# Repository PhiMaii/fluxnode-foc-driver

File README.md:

# FluxNode-FOC

FluxNode-FOC is a compact, general-purpose BLDC motor controller designed for field-oriented control in robotics, actuators, experimental drives, and motor-integrated applications.

The project combines a high-performance STM32G4 microcontroller, a three-phase MOSFET power stage, three-phase current sensing, rotor position sensing, phase-voltage measurement, CAN-FD communication, USB, temperature monitoring, and an optional brake chopper.

The design is intended to be understandable, repairable, and extensible rather than optimized only for minimum cost or minimum PCB area.

> **Project status:** Hardware and firmware architecture are still under development. Electrical values, component selections, interfaces, and PCB details may change before the first validated hardware revision.

---

## 1. Main design targets

| Parameter | Target |
|---|---:|
| Battery voltage | Up to 8S Li-ion/LiPo |
| Maximum normal battery voltage | 33.6 V |
| Design measurement range | Up to approximately 40 V |
| Nominal development voltage | 24 V |
| Continuous phase current target | Approximately 8 A RMS |
| Peak current target | Approximately 20 A |
| PWM frequency | 25 kHz |
| Control method | Field-oriented control |
| Power MOSFET voltage rating | 60 V |
| Bulk capacitor voltage rating | 50–63 V |
| Main communication interface | CAN-FD |
| MCU | STM32G474RE |
| Gate driver | DRV8323SRTAR |
| Main rotor encoder | AS5047P |
| PCB stackup | 6 layers preferred |

The controller is designed around **8S operation**, not 10S. A fully charged 8S battery reaches 33.6 V. Additional margin is required for wiring inductance, regenerative braking, switching transients, and load-disconnect events.

The system may be operated from lower voltages, including a 24 V laboratory supply, as long as the supply is compatible with regenerative energy or appropriate braking and overvoltage protection are provided.

---

## 2. Design philosophy

The main design priorities are:

1. Reliable and accurately timed current measurement for FOC.
2. Low-inductance power-stage layout.
3. Sufficient voltage margin for an 8S battery system.
4. Good observability through current, voltage, temperature, and diagnostic measurements.
5. Expandability for different motors, sensors, and actuator configurations.
6. Firmware that is understandable and not tightly coupled to a single framework.
7. Practical assembly and debugging with commonly available tools.

The design intentionally includes features that are not strictly required for basic FOC, such as phase-voltage sensing, several temperature channels, CAN-FD, an auxiliary sensor interface, and an optional brake chopper. These features make the controller more useful as a development platform and provide additional diagnostic and protection options.

---

## 3. System architecture

The controller is divided into the following main functional blocks:

- Power input and protection
- Auxiliary power supplies
- STM32G474 control section
- DRV8323 gate driver
- Three-phase MOSFET bridge
- Three-phase current measurement
- Phase-voltage and DC-bus voltage measurement
- Rotor-position sensing
- Temperature monitoring
- CAN-FD and USB communication
- Optional external sensor interfaces
- Optional brake chopper
- Fan and debug outputs

The KiCad schematic should remain split into logical hierarchical sheets rather than placing the entire design on one sheet.

Suggested schematic sheets:

```text
Power Input
Power Supplies
MCU Core
Gate Driver
Power Stage
Current Sense
Voltage Sense
Encoders and Sensors
CAN and USB
Temperature and Fan
Brake Chopper
Debug and Expansion
```

---

## 4. Microcontroller

The selected MCU is the **STM32G474RE**, based on the STM32G4 family.

Reasons for selecting this MCU include:

- High-performance Cortex-M4 core
- Floating-point unit
- Advanced motor-control timers
- Multiple fast ADCs
- Internal operational amplifiers and comparators
- CORDIC and FMAC accelerators
- Multiple SPI peripherals
- FDCAN support
- USB device support
- DAC outputs
- Good support through STM32CubeMX and STM32Cube firmware packages

The STM32G474xB/xC/xE datasheet is the reference MCU datasheet for this project.

### Motor-control timer

TIM1 is reserved for the three-phase complementary PWM outputs.

The current pin allocation uses:

- TIM1 channel 2 and channel 2N
- TIM1 channel 3 and channel 3N
- TIM1 channel 4 and channel 4N

TIM1 channel 4 on the selected STM32G474 package has a complementary output and can therefore be used as one of the three half-bridge PWM channels.

TIM1 should be configured for:

- Center-aligned PWM
- Complementary outputs
- Programmable dead time
- Break input support
- 25 kHz switching frequency
- ADC trigger generation at defined points in the PWM cycle

The exact output polarity and idle states must match the DRV8323 input configuration.

---

## 5. Gate driver

The selected gate driver is the **DRV8323SRTAR**.

It provides:

- Three half-bridge gate-drive channels
- SPI configuration and diagnostics
- Adjustable gate-drive strength
- Current-shunt amplifier support
- Fault reporting
- Undervoltage and overcurrent protection features

The gate driver is connected to the STM32 through:

- Six PWM signals
- SPI clock, COPI, CIPO, and chip select
- Enable signal
- nFAULT signal
- Optional additional diagnostic signals
- Analog VREF generated by an MCU DAC

### Gate-driver SPI

The gate driver shares SPI1 with the onboard magnetic encoder. Each device has a separate chip-select signal and is accessed sequentially.

This sharing is acceptable because neither device requires continuous full-bandwidth SPI traffic. Motor-control timing must not depend on slow or blocking SPI transactions.

The external auxiliary SPI connector uses SPI3 so that optional external hardware does not disturb the main gate-driver and encoder bus.

### nFAULT

The gate-driver fault output should be connected to an interrupt-capable GPIO input.

Software should log and decode the driver fault registers, but hardware protection must not rely only on software response time. Where practical, the timer break input should be used for immediate PWM shutdown.

### VREF

The DRV8323 current-sense amplifier reference is generated by a DAC output from the STM32 rather than being permanently tied to 3.3 V.

This allows the current-sense zero point to be adjusted in firmware. The DAC output must be properly decoupled and kept quiet because noise on VREF directly affects all current measurements.

---

## 6. Power stage

The three-phase inverter uses six external N-channel MOSFETs.

The currently selected phase MOSFET is:

- **TPW1R306PL**

The design uses 60 V MOSFETs to provide useful margin above the 33.6 V maximum battery voltage. This margin is still not sufficient by itself to tolerate uncontrolled regenerative voltage rise or poor PCB layout, so transient suppression and bus-voltage monitoring remain necessary.

### Power-stage layout priorities

The following loops must be kept as small as possible:

- High-side MOSFET, low-side MOSFET, and local ceramic/bulk capacitor commutation loop
- Gate-driver source and sink loops
- Bootstrap capacitor loops
- Current-shunt measurement loops

The gate driver and gate resistors must be placed close to the MOSFETs. Gate traces should be short, direct, and separated from high-current switching nodes.

Kelvin source connections should be used where practical for gate-drive return and current measurement.

The phase nodes are high-dV/dt switching nodes and should have limited copper area. They should not run beneath sensitive analog circuits, the encoder, the crystal, USB, or communication interfaces.

---

## 7. Power input and voltage protection

The input stage is designed for an 8S battery or a suitable DC supply.

Required or planned protection includes:

- Reverse-polarity protection where practical
- Input fuse or external fused supply
- TVS diode or equivalent transient suppression
- Local ceramic decoupling close to the bridge
- 50–63 V rated bulk capacitors
- DC-bus voltage measurement
- Firmware overvoltage and undervoltage limits
- Optional brake chopper
- Consideration of regenerative current into the source

The exact TVS voltage must be selected together with the maximum allowed bus voltage, MOSFET rating, gate-driver rating, and expected transient energy. It must not clamp during normal 8S operation but must act before the power stage is exposed to unsafe voltage.

A bench supply may not be able to absorb regenerative current. Motor deceleration can therefore raise the bus voltage even when the controller is powered from a regulated supply.

---

## 8. Current sensing

The design measures all three phase currents.

Each phase has its own shunt measurement path, allowing:

- Three-phase current reconstruction
- More flexible sampling
- Better diagnostics
- Detection of measurement inconsistencies
- Improved operation in modulation regions where two-shunt measurement becomes difficult

The phase-current channels are distributed across separate ADCs where possible so that they can be sampled simultaneously or with minimal timing skew.

The current measurements are configured as injected ADC conversions triggered by TIM1. Sampling should occur at a defined low-noise point in the PWM cycle.

Important requirements:

- Use differential/Kelvin routing from each shunt.
- Keep current-sense traces away from phase nodes and gate traces.
- Place input filtering near the receiving amplifier or ADC input as appropriate.
- Keep the three channels electrically symmetrical.
- Calibrate current offsets before enabling the power stage.
- Recheck offsets when temperature or VREF changes significantly.
- Detect ADC saturation and implausible current combinations.

Phase-current ADCs should remain the highest-priority analog measurements. Slower signals such as temperature and battery voltage should use regular conversions or lower-priority ADC resources.

---

## 9. Phase-voltage sensing

All three motor phases are measured through resistor dividers.

Phase-voltage sensing is not required for basic encoder-based FOC, but it provides several useful capabilities:

- Back-EMF observation
- Sensorless experimentation
- Motor-state diagnostics
- Phase-disconnection detection
- Verification of switching behavior
- Improved startup and fault analysis
- Potential observer development

The chosen divider concept uses two series high-side resistors and one low-side resistor to distribute voltage stress and improve routing.

The currently considered common value set is:

```text
High side: 2 × 51 kΩ
Low side: 6.8 kΩ
```

This ratio provides margin for phase and bus voltage excursions near 40 V while keeping the ADC voltage within the 3.3 V domain.

The final divider values must be verified against:

- ADC absolute maximum voltage
- Resistor tolerance
- Maximum expected transient voltage
- ADC input leakage
- Sampling-time requirements
- Desired measurement bandwidth

A small capacitor at the ADC-side divider node provides anti-aliasing and switching-noise filtering. A value around **1 nF** is currently considered for the phase-voltage channels, subject to final simulation and measurement.

The divider resistors should be placed close to the phase-sense pickup, while the final filter capacitor and any small series protection resistor should be placed close to the MCU ADC input. Routing between the divider and MCU must avoid switching nodes.

The phase voltages should be sampled from a timer-derived trigger at a repeatable point in the PWM cycle. They do not necessarily need the same timing priority as the phase currents.

---

## 10. DC-bus voltage sensing

The battery/DC-bus voltage is measured by an external resistor divider connected to an ADC channel.

The MCU VBAT pin is not used for measuring the motor supply. The external motor bus can reach approximately 40 V during transients and requires a dedicated divider.

The bus-voltage channel is used for:

- Undervoltage protection
- Overvoltage protection
- Brake-chopper control
- Regenerative-braking management
- Power and energy estimation
- Supply diagnostics

The same general divider ratio as the phase-voltage measurement may be used to simplify the bill of materials:

```text
High side: 2 × 51 kΩ
Low side: 6.8 kΩ
```

The bus voltage changes much more slowly than the phase-node voltage, so it should use stronger filtering than the phase-voltage channels. The final capacitor value should be chosen based on the desired brake-chopper response and ADC sampling rate.

The divider must be connected directly to the actual power-stage DC bus rather than to a remote or lightly loaded supply node.

---

## 11. Rotor-position sensing

The main onboard rotor encoder is the **AS5047P**.

It is connected by SPI and is intended to provide the rotor angle used by the FOC algorithm.

Reasons for choosing the AS5047P include:

- 14-bit absolute angle output
- High-speed SPI interface
- Suitability for motor-control applications
- On-chip dynamic angle error compensation
- Diagnostic information
- Common use in compact BLDC actuators

The encoder shares SPI1 with the DRV8323, using a separate chip-select signal.

Encoder transactions should be:

- Short
- Deterministic
- Checked for communication and parity errors
- Scheduled so they do not interfere with the current-control interrupt

DMA may be added later if it measurably improves timing or CPU load, but it is not required for initial firmware bring-up.

The PCB must respect the encoder manufacturer's magnet alignment, air-gap, magnetic-field, and keepout recommendations.

An additional external sensor interface is available through SPI3. This may be used for:

- A second encoder
- An off-axis sensor
- An external actuator sensor
- Experimental sensors

The external sensor is optional and not required for initial operation.

---

## 12. ADC allocation philosophy

The STM32G474 provides multiple ADCs, which are used to separate timing-critical and slow measurements.

The allocation philosophy is:

- Distribute the three phase-current measurements across ADC1, ADC2, and ADC3 where possible.
- Use injected conversions triggered by TIM1 for phase currents.
- Place phase-voltage measurements on available ADC channels, even when one ADC must contain two phase-voltage channels.
- Use regular conversions for bus voltage and temperature measurements.
- Use ADC4 and ADC5 for lower-priority auxiliary measurements where convenient.
- Avoid sacrificing correct phase-current timing merely to make the ADC channel allocation look symmetrical.

Current and phase-voltage measurements may share an ADC if the injected and regular sequences are configured carefully. The timing-critical current conversion always has priority.

---

## 13. Temperature monitoring

Planned temperature measurements include:

- Power MOSFET temperature
- Motor temperature
- Brake-chopper resistor or chopper-stage temperature
- MCU internal temperature

External temperatures are measured with NTC resistor dividers connected to ADC inputs.

Temperature monitoring is used for:

- Warning thresholds
- Current derating
- Fan control
- Controlled shutdown
- Fault logging

The MCU internal temperature sensor can be sampled in addition to the external channels. It is useful for board-level thermal monitoring but does not replace a sensor close to the MOSFETs.

NTC channels are slow signals and do not require timer-synchronous sampling.

---

## 14. Brake chopper

An optional brake chopper is included to prevent excessive DC-bus voltage during regenerative braking.

The brake chopper consists of:

- A power MOSFET
- Gate-drive circuitry
- An external or onboard braking resistor connection
- Bus-voltage feedback
- Temperature monitoring where practical
- Firmware control and fault limits

The braking resistor may be implemented as an external add-on connected through a dedicated power connector. This avoids placing a large, hot resistor on the compact controller PCB.

The chopper is controlled from a timer PWM output. It is currently assigned separately from the fan PWM so that both functions can operate independently.

The chopper is activated based on the measured DC-bus voltage. Typical firmware behavior will include:

1. Chopper remains off below the activation threshold.
2. PWM duty increases when the bus exceeds the target voltage.
3. Duty is reduced as the bus voltage falls.
4. A higher emergency threshold disables motor PWM if the chopper cannot control the bus.
5. Temperature and maximum duty limits protect the MOSFET and resistor.

The exact voltage thresholds depend on the final TVS selection, capacitor rating, MOSFET margin, and maximum permitted bus voltage.

The brake chopper must default to off during reset and startup.

---

## 15. Communication interfaces

### CAN-FD

CAN-FD is the main external real-time communication interface.

It is intended for:

- Commands and setpoints
- Telemetry
- Fault reporting
- Parameter configuration
- Multi-axis systems
- Daisy-chain-style wiring between actuator nodes

Electrical CAN wiring is a bus, not a logical point-to-point daisy chain. Connectors may provide CAN in and CAN out for convenient physical chaining, but all nodes share the same differential bus.

The controller should include:

- CAN transceiver
- CANH and CANL routing as a differential pair
- Optional switchable termination
- ESD protection near the connector
- Ground reference
- Suitable connector pinout for repeated nodes

Termination should only be enabled at the two physical ends of the CAN bus.

### USB-C

USB-C provides a local interface for:

- Firmware development
- Configuration
- Diagnostics
- Bootloader or device firmware update
- High-rate local telemetry where useful

USB is not intended to power the motor stage.

The USB section includes:

- USB 2.0 full-speed D+ and D−
- 22 Ω series resistors close to the MCU
- ESD protection close to the connector
- Correct USB-C CC resistors for a device
- VBUS sensing
- Protection against unwanted back-powering when USB and the motor battery are connected simultaneously

USB 5 V and the board's main supply must not be directly tied together without a deliberate power-path design.

---

## 16. Auxiliary interfaces

The board includes optional external interfaces for future sensors and accessories.

Planned interfaces include:

- SPI3 auxiliary sensor port
- I2C sensor port
- Fan connector
- External brake-resistor connector
- SWD debugging connector
- Debug LEDs
- Optional spare GPIO or timer signals where routing permits

The external SPI port is separate from the main SPI1 bus. This prevents an optional cable-connected device from adding excessive capacitance or noise to the gate-driver and onboard-encoder interface.

I2C is intended for relatively slow optional sensors. Pull-up resistors should be configurable or removable so that multiple boards or sensor modules do not unintentionally place too many pull-ups in parallel.

---

## 17. Fan control

An external fan can be controlled through a timer PWM output.

The fan output is independent of the brake-chopper PWM.

Firmware may control fan speed based on:

- MOSFET temperature
- Motor current
- Board temperature
- Brake-chopper activity
- User configuration

The MCU pin must not directly drive a fan motor. A suitable transistor or MOSFET stage, flyback protection where required, and connector decoupling must be provided.

---

## 18. Debugging and programming

The primary programming and debugging interface is SWD.

Required signals include:

- SWDIO
- SWCLK
- NRST
- GND
- Target reference voltage
- Optional SWO

SWO should be routed if pin availability allows it, because it can provide low-overhead debug output and timing information.

Boot configuration and reset access should remain available during bring-up.

At least two debug LEDs are planned for basic status and fault indication.

---

## 19. PCB stackup and layout

A **6-layer PCB** is preferred.

Although a 4-layer design is technically possible, the small additional fabrication cost of six layers is justified by the complexity of the mixed-signal motor-control board.

A possible six-layer stackup is:

```text
L1: Components, short signals, power-stage copper
L2: Solid ground plane
L3: Power distribution
L4: Secondary power and slower signals
L5: Solid ground plane
L6: Signals and low-current components
```

The exact stackup must be selected from the PCB manufacturer's controlled stackup options.

### Reasons for using six layers

- Better uninterrupted ground references
- Easier separation of power and sensitive analog routing
- Improved return-current paths
- More practical routing around the LQFP MCU
- Better EMI performance
- Easier CAN, USB, SPI, and ADC routing
- Reduced need to split or perforate the main ground plane

### Ground strategy

The design should use a continuous ground system rather than creating isolated analog and digital ground islands.

Sensitive analog circuits should be separated by placement and return-current control, not by cutting the ground plane.

High-current power returns must not share narrow copper paths with:

- ADC reference returns
- Current-sense returns
- Encoder ground
- USB ground
- MCU decoupling returns

Use stitching vias around noisy power areas, board edges where appropriate, and layer transitions.

### Placement order

Recommended placement order:

1. MOSFET bridge and power connectors
2. DC-link capacitors
3. Gate driver and gate components
4. Current shunts and sense paths
5. MCU and decoupling
6. Encoder
7. Power supplies
8. CAN and USB
9. Auxiliary connectors
10. Debug and low-priority circuitry

The power-stage layout should be completed before general digital routing.

---

## 20. Component sizes and assembly

The board uses a mixture of 0402 and 0603 passives.

General preference:

- Use 0402 where density or very low parasitic inductance matters.
- Use 0603 for resistor dividers, manually reworked parts, and components exposed to higher voltage.
- Use appropriately larger packages for high-power, high-voltage, or high-capacitance components.
- Do not select 0402 only to reduce board area if it makes probing and rework unnecessarily difficult.

For voltage dividers connected to the motor bus or phase nodes, 0603 resistors are preferred. Splitting the high-side resistance between two components reduces the voltage across each resistor and improves layout flexibility.

The PCB is intended to be assembled with solder paste, hot plate or reflow, hot air, flux, and hand rework where necessary. 0402 assembly is possible but requires careful paste control and inspection.

---

## 21. Firmware workflow

The firmware is generated initially with **STM32CubeMX** and developed in **Visual Studio Code**.

PlatformIO is not used for this project.

The intended workflow is:

1. Configure pins, clocks, ADCs, timers, DMA, communication peripherals, and middleware in STM32CubeMX.
2. Generate the STM32 project and initialization code.
3. Open and develop the generated project in Visual Studio Code.
4. Keep application code outside generated sections where possible.
5. Regenerate from CubeMX without overwriting project logic.
6. Build and debug using the selected ARM GCC/CMake or STM32-compatible toolchain.

The firmware will initially use STM32 HAL and LL drivers where appropriate. Time-critical motor-control code may use LL access or direct register operations after the basic system is validated.

### Firmware language

CubeMX generates C initialization code. The main firmware may remain primarily C, with carefully introduced C++ modules if they offer a clear architectural benefit.

The project should not depend on CubeMX generating native C++ code. C-generated peripheral initialization can be called from C++ through a compatible interface.

### Real-time priorities

Highest-priority operations include:

- PWM update
- Current sampling
- Current-control loop
- Hardware fault response

Lower-priority operations include:

- Encoder communication
- CAN processing
- USB communication
- Temperature conversion
- Logging
- Configuration storage
- User-interface functions

Blocking operations must not be used inside the fast control interrupt.

FreeRTOS is not required for the initial motor-control implementation. It may be evaluated later if the communication and application layers become complex enough to justify it.

---

## 22. Suggested repository structure

The project uses a single repository containing hardware, firmware, documentation, and tools.

```text
FluxNode-FOC/
├── README.md
├── LICENSE
├── .gitignore
├── docs/
│   ├── architecture/
│   ├── calculations/
│   ├── bring-up/
│   ├── measurements/
│   └── images/
├── hardware/
│   ├── kicad/
│   │   ├── FluxNode-FOC.kicad_pro
│   │   ├── FluxNode-FOC.kicad_sch
│   │   ├── FluxNode-FOC.kicad_pcb
│   │   └── sheets/
│   ├── libraries/
│   │   ├── symbols/
│   │   ├── footprints/
│   │   └── 3dmodels/
│   ├── production/
│   │   ├── gerbers/
│   │   ├── bom/
│   │   ├── pick-and-place/
│   │   └── assembly/
│   └── datasheets/
├── firmware/
│   ├── cubemx/
│   ├── Core/
│   ├── Drivers/
│   ├── App/
│   ├── MotorControl/
│   ├── Communication/
│   ├── BSP/
│   ├── Tests/
│   └── tools/
├── mechanical/
│   ├── cad/
│   ├── drawings/
│   └── exports/
└── scripts/
```

A monorepo is preferred because hardware and firmware revisions are tightly coupled. A tag or release can therefore identify the exact PCB, schematic, firmware, configuration, and documentation that belong together.

Generated production files should be placed in clearly versioned release folders or attached to Git releases rather than continuously overwriting unversioned files.

Large vendor libraries should not be copied into the repository unless their license permits it and they are required for reproducible builds.

---

## 23. Naming and revision conventions

Suggested conventions:

- Repository: `FluxNode-FOC`
- Firmware modules: lowercase or project-standard snake_case
- PCB revision: `REV_A`, `REV_B`, and so on
- Firmware semantic version: `v0.1.0`, `v0.2.0`, and so on
- Hardware-specific firmware configuration: explicitly tied to a PCB revision
- Nets: descriptive uppercase names such as `VBUS`, `PHASE_A`, `ISENSE_A`, and `DRV_NFAULT`

Each manufactured PCB revision should have a visible revision marking on the silkscreen.

Firmware should check or store the expected hardware revision where practical.

---

## 24. Bring-up strategy

Initial bring-up should be performed in controlled stages.

### Stage 1: Unpowered checks

- Visual inspection
- Resistance checks between all power rails and ground
- Verify MOSFET orientation
- Verify gate-driver and MCU pin orientation
- Check for solder bridges
- Check shunt and divider values
- Confirm connector polarity

### Stage 2: Low-voltage control power

- Use a current-limited supply
- Verify all regulated rails
- Confirm MCU programming and SWD
- Check reset and clock operation
- Test debug LEDs
- Verify USB without motor power

### Stage 3: Gate driver without motor operation

- Read and write SPI registers
- Confirm nFAULT behavior
- Verify DAC-generated VREF
- Observe PWM outputs with the bridge disabled
- Verify dead time and complementary polarity

### Stage 4: Power-stage switching

- Use a low DC-bus voltage
- Use strict current limiting
- Test one half bridge at a time where practical
- Observe gate voltage, switch node, and ringing
- Verify bootstrap operation
- Tune gate resistors only after measurements

### Stage 5: Sensor validation

- Calibrate current offsets
- Inject known current where possible
- Verify bus and phase-voltage scaling
- Check all NTC channels
- Verify encoder direction, zero, and diagnostics

### Stage 6: First motor operation

- Use a small motor and low bus voltage
- Start with limited voltage and current commands
- Validate phase order
- Validate encoder direction and electrical offset
- Test open-loop rotation before closed-loop current control
- Keep overcurrent and overvoltage limits conservative

### Stage 7: Full-power validation

- Increase voltage and current gradually
- Measure MOSFET and gate-driver temperature
- Validate bus transients
- Test regenerative braking
- Validate brake-chopper behavior
- Perform sustained thermal tests

---

## 25. Safety

This project controls motors from battery voltages and currents capable of causing burns, fire, component explosion, mechanical injury, and battery damage.

Development precautions include:

- Use a current-limited power source during bring-up.
- Add an appropriate fuse.
- Keep a physical emergency disconnect accessible.
- Secure the motor mechanically.
- Do not touch the board while powered.
- Use differential or isolated probing techniques for switching-node measurements.
- Do not connect an oscilloscope ground clip to a non-ground switching node.
- Treat lithium batteries as high-energy sources.
- Verify braking behavior before high-speed operation.
- Test overvoltage protection before relying on regenerative braking.

The controller is an experimental design and is not certified for safety-critical use.

---

## 26. Open design decisions

The following items are not yet final and must be confirmed before release:

- Final CAN transceiver and connector pinout
- Final auxiliary power-supply topology
- Final TVS diode and overvoltage thresholds
- Exact current-shunt resistance and power rating
- Current-sense amplifier gain and filtering
- Final voltage-divider capacitor values
- Brake-chopper MOSFET, gate driver, resistor rating, and connector
- Final fan voltage and output stage
- Exact ADC channel allocation
- Final SPI clock rates
- DMA usage for encoder and communication peripherals
- USB device class
- Final board dimensions and mounting pattern
- Final six-layer manufacturer stackup
- Exact thermal limits and current-derating curve
- Production test-point set
- Bootloader and firmware-update strategy

These items should be moved out of this section once they are validated and formally adopted.

---

## 27. Documentation policy

Important design decisions should be documented in the repository rather than existing only in chat logs or schematic comments.

For every major decision, record:

- What was selected
- Why it was selected
- Alternatives considered
- Important calculations
- Validation measurements
- Any revision-specific limitations

Hardware calculations, oscilloscope captures, thermal tests, and bring-up notes should be stored under `docs/`.

Datasheets should either be linked from documentation or stored under `hardware/datasheets/` when redistribution is permitted.

---

## 28. License

A license has not yet been finalized.

Before publishing the repository, choose separate or compatible licenses for:

- Hardware design files
- Firmware
- Documentation

Common choices include CERN-OHL for hardware and MIT, BSD, GPL, or Apache-2.0 for firmware. The final choice should reflect whether commercial reuse and closed-source derivatives are intended to be allowed.

---

## 29. Current project summary

The current FluxNode-FOC concept is a 6-layer, STM32G474-based FOC motor controller for up to 8S operation. It uses a DRV8323 SPI gate driver, external 60 V MOSFETs, three phase-current measurements, three phase-voltage measurements, DC-bus sensing, an AS5047P rotor encoder, CAN-FD, USB-C, temperature monitoring, fan control, and an optional external-resistor brake chopper.

The firmware is generated with STM32CubeMX and developed in Visual Studio Code without PlatformIO.

The project remains under active development, and all high-power functionality must be validated experimentally before the design is considered complete.

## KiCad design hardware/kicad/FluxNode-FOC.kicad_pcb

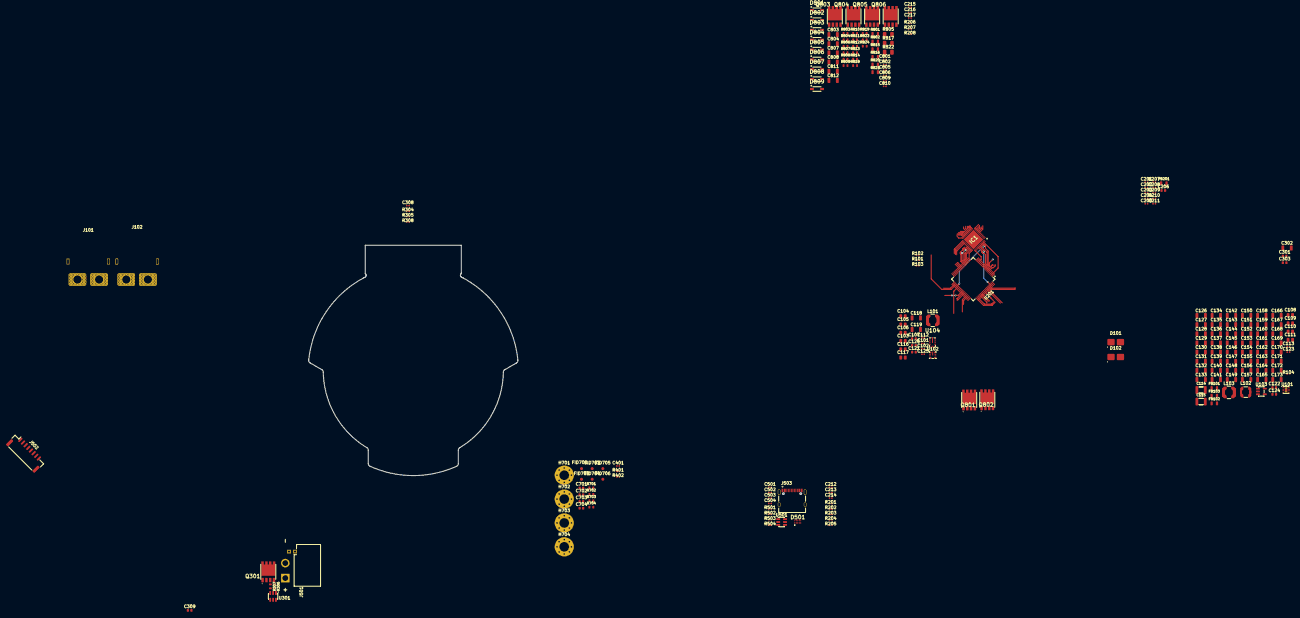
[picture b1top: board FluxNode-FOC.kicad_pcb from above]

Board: 6 copper layers, 216 parts (0 on the bottom side), 93 nets.

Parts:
C101, C102, C113: 100nF X7R 50V; C_0402_1005_DensityHigh
C103, C111: 22uF X7R 10V; C_0805_2012_DensityHigh
C104, C116: 2u2 X7R 100V; C_0805_2012_DensityHigh
C105, C106, C108, C109, C117: 2u2 100V; C_0805_2012_DensityHigh
C107, C303: 100nF 100V; C_0603_1608_DensityHigh
C110: 10u 25V; C_0805_2012_DensityHigh
C112, C201, C209: 1uF X7R 10V; C_0402_1005_DensityHigh
C114, C115: 15uF 25V; C_1210_3225_DensityHigh
C118, C119, C302: 4u7 100V; C_1206_3216_DensityHigh
C120, C121: 220n 100V; C_0603_1608_DensityHigh
C122, C301: 1u 25V; C_0603_1608_DensityHigh
C123: 10n 100V; C_0402_1005_DensityHigh
C124, C206: 4.7u 16V; C_0603_1608_DensityHigh
C125: 1u X7R 10V; C_0402_1005_DensityHigh
C126, C127, C128, C129, C130, C131, C132, C133, C134, C135, C136, C137, C138, C139, C140, C141, C142, C143, C144, C145, C146, C147, C148, C149, C150, C151, C152, C153, C154, C155, C156, C157, C158, C159, C160, C161, C162, C163, C164, C165, C166, C167, C168, C169, C170, C171, C172, C173, C803, C808, C812: 4.7u 100V; C_1206_3216_DensityHigh
C202, C203, C204, C205, C208, C210, C401: 100n 50V; C_0402_1005_DensityHigh
C207: 1uF 10V; C_0402_1005_DensityHigh
C211: 4.7u X5R 25V; C_0402_1005_DensityHigh
C212, C213, C214: 1nF 25V; C_0402_1005_DensityHigh
C215, C216, C217: 470pF 50V; C_0402_1005_DensityHigh
C308, C503, C504: 100nF 50V; C_0402_1005_DensityHigh
C309: 1uF 50V; C_0603_1608_DensityHigh
C501, C502: 100nF; C_0402_1005_DensityHigh
C701, C702, C703, C704: 1nF 1kV; C_0603_1608_DensityHigh
C801, C802, C805, C806, C809, C810: 3n3 10% 100V; C_0402_1005_DensityHigh
C804, C807, C811: 100nF 100V; C_1206_3216_DensityHigh
D101, D102: SMBJ51CD-M3_H; DIOM4336X24N
D501: PESD4USB3U-TBSX; PESD4USB3UTBSX
D801, D802, D803, D804, D805, D806, D807, D808, D809: BAT41ZFILM; SOD3816X145N
FB101, FB102, FB103, FB201: 1k @ 100MHz; R_0805_2012_DensityHigh
FID701, FID702, FID703, FID704, FID705, FID706: Fiducial; Fiducial_1mm_Mask2mm
H701, H702, H703, H704: MountingHole_Pad; MountingHole_3.2mm_M3_Pad_Via
IC1: DRV8323SRTAR; QFN50P600X600X80-41N-D
J101: XT60PW-F; AMASS_XT60PW-F_1x02_P7.20mm_Horizontal
J102: XT60PW-M; AMASS_XT60PW-M_1x02_P7.20mm_Horizontal
J501: XT30PW_2_2_-M.G.B; AMASS_XT30PW_2_2_-M.G.B
J502: Conn_01x08_Pin; JST_GH_SM08B-GHS-TB_1x08-1MP_P1.25mm_Horizontal
J503: TYPE-C-31-M-12; HRO_TYPE-C-31-M-12
L101, L103: 22uH 830mA 360mOhms; L_Coilcraft_LPS4018
L102: 2.2uH 1,2A 100mOhms; L_Coilcraft_LPS3314
Q301, Q801, Q802, Q803, Q804, Q805, Q806: TPW1R306PL; SOP_ADVANCE
R101: 10k 1% 50V; R_0402_1005_DensityHigh
R102: 0R; R_0402_1005_DensityHigh
R103: 100k 1% 50V; R_0402_1005_DensityHigh
R104: 9.09k 1% 50V; R_0402_1005_DensityHigh
R201, R202, R203, R204, R205: 22R 1%; R_0402_1005_DensityHigh
R206, R207, R208: 1K 1%; R_0402_1005_DensityHigh
R304: 100; R_0402_1005_DensityHigh
R305: 10k; R_0402_1005_DensityHigh
R306: 4.7; R_0603_1608_DensityHigh
R307: 1.5; R_0603_1608_DensityHigh
R308: 47k; R_0402_1005_DensityHigh
R401: 100k 1%; R_0402_1005_DensityHigh
R402: 8k2 1%; R_0402_1005_DensityHigh
R501, R502: 5k1 1%; R_0402_1005_DensityHigh
R503, R504: 100k; R_0402_1005_DensityHigh
R701, R702, R703, R704: 0R; R_0603_1608_DensityHigh
R801, R802, R815, R816, R820, R821: 7.5 1% 0.5W; R_0805_2012_DensityHigh
R803, R804, R818, R819, R823, R824: 5R 1% 0.4W; R_0603_1608_DensityHigh
R805, R817, R822: 0.5m 1% 2W; R_1206_3216_DensityHigh
R806, R807, R809, R810, R812, R813: 43k 1% 75V; R_0603_1608_DensityHigh
R808, R811, R814: 6k8 1% 75V; R_0603_1608_DensityHigh
U101: TPS62172DSG; WSON-8-1EP_2x2mm_P0.5mm_EP0.9x1.6mm_ThermalVias
U102: LMR36506MSC5RPERQ1; LMR36503
U103: LP2992IM5-3.3/NOPB; SOT-23-5
U104: LMR36006FSCQ; LMR36006
U201: STM32G474RET6; LQFP-64_10x10mm_P0.5mm
U301: UCC27511ADBV; SOT-23-6
U501: USBLC6-2SC6; SOT-23-6

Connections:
+3V3: C111.1, C201.1, C202.1, C203.1, C204.1, C205.1, C206.1, C503.1, L102.2, U201.1 (VBAT), U201.16 (VDD), U201.32 (VDD), U201.48 (VDD), U201.64 (VDD)
+5V: C102.1, C103.1, C108.1, C122.1, FB102.1, L101.2, R101.1, U103.1 (VIN)
+12V: C114.1, C115.1, C308.1, C309.1, L103.2, U301.1 (V_{DD})
+A3V3: C124.1, C209.1, FB201.2, IC1.24 (VREF), U103.5 (VOUT)
+VBAT: C104.1, C116.1, C126.1, C127.1, C128.1, C129.1, C130.1, C131.1, C132.1, C133.1, C134.1, C135.1, C136.1, C137.1, C138.1, C139.1, C140.1, C141.1, C142.1, C143.1, C144.1, C145.1, C146.1, C147.1, C148.1, C149.1, C150.1, C151.1, C152.1, C153.1, C154.1, C155.1, C156.1, C157.1, C158.1, C159.1, C160.1, C161.1, C162.1, C163.1, C164.1, C165.1, C166.1, C167.1, C168.1, C169.1, C170.1, C171.1, C172.1, C173.1, C301.1, C302.1, C303.1, C803.1, C804.1, C807.1, C808.1, C811.1, C812.1, D101.2, D102.2, FB101.1, FB103.1, IC1.4 (VM), IC1.5 (VDRAIN), J101.2, J102.2, J501.P, Q801.5 (D), Q801.6 (D), Q801.7 (D), Q801.8 (D), Q803.5 (D), Q803.6 (D), Q803.7 (D), Q803.8 (D), Q805.5 (D), Q805.6 (D), Q805.7 (D), Q805.8 (D), R401.1, R803.2, R818.2, R823.2
/01 Power Generation/5V_VIN_3V3: C109.1, C110.1, FB102.2, U101.2 (VIN)
/01 Power Generation/ADJ_A3V3: C123.1, U103.4 (ADJ)
/01 Power Generation/BOOT_5V: C101.2, U102.6 (BOOT)
/01 Power Generation/BOOT_12V: C113.2, U104.4 (BOOT)
/01 Power Generation/FB_DIV_12V: R103.2, R104.1, U104.7 (FB)
/01 Power Generation/F_VIN_5V: C105.1, C106.1, C107.1, FB101.2, U102.3 (EN/UVLO), U102.4 (VIN)
/01 Power Generation/F_VIN_12V: C117.1, C118.1, C119.1, C120.1, C121.1, FB103.2, U104.2 (VIN), U104.9 (EN), U104.10 (VIN)
/01 Power Generation/PG_5V: R101.2, U101.3 (EN), U102.2 (PGOOD), U103.3 (ON/~OFF)
/01 Power Generation/SW_3V3: L102.1, U101.7 (SW)
/01 Power Generation/SW_5V: C101.1, L101.1, U102.5 (SW)
/01 Power Generation/SW_12V: C113.1, L103.1, U104.3 (NC), U104.12 (SW)
/02 MCU/BRAKE_CTRL: R304.2, U201.41 (PC9)
/02 MCU/DRV_CAL: IC1.31 (CAL), U201.14 (PA2)
/02 MCU/DRV_EN: IC1.30 (ENABLE), U201.17 (PA3)
/02 MCU/DRV_PWM_HA: IC1.34 (INHA), U201.10 (PC2)
/02 MCU/DRV_PWM_HB: IC1.36 (INHB), U201.9 (PC1)
/02 MCU/DRV_PWM_HC: IC1.38 (INHC), U201.8 (PC0)
/02 MCU/DRV_PWM_LA: IC1.35 (INLA), U201.62 (PB9)
/02 MCU/DRV_PWM_LB: IC1.37 (INLB), U201.36 (PB14)
/02 MCU/DRV_PWM_LC: IC1.39 (INLC), U201.2 (PC13)
/02 MCU/DRV_SOA_FILT: C212.1, R201.1, U201.24 (PB0)
/02 MCU/DRV_SOB_FILT: C213.1, R202.1, U201.25 (PB1)
/02 MCU/DRV_SOC_FILT: C214.1, R203.1, U201.26 (PB2)
/02 MCU/DRV_nFAULT: IC1.25 (NFAULT), U201.22 (PC4)
/02 MCU/F_A3V3: C207.1, C208.1, C210.1, C211.1, FB201.1, U201.28 (VREF+), U201.29 (VDDA)
/02 MCU/NRST: C504.1, D501.1 (K), D501.10 (K), U201.7 (PG10)
/02 MCU/SENSE_UA: C215.1, R206.1, U201.11 (PC3)
/02 MCU/SENSE_UB: C216.1, R207.1, U201.13 (PA1)
/02 MCU/SENSE_UC: C217.1, R208.1, U201.12 (PA0)
/02 MCU/SENSE_VBAT: C401.1, R401.2, R402.1, U201.35 (PB13)
/02 MCU/SOA: IC1.23 (SOA), R201.2
/02 MCU/SOB: IC1.22 (SOB), R202.2
/02 MCU/SOC: IC1.21 (SOC), R203.2
/02 MCU/SPI1_DRV_CS: IC1.29 (NSCS), U201.18 (PA4)
/02 MCU/SPI1_MISO: IC1.26 (SDO), U201.20 (PA6)
/02 MCU/SPI1_MOSI: IC1.27 (SDI), U201.21 (PA7)
/02 MCU/SPI1_SCK: IC1.28 (SCLK), U201.19 (PA5)
/02 MCU/SWCLK: D501.4 (K), D501.7 (K), U201.50 (PA14)
/02 MCU/SWDIO: D501.5 (K), D501.6 (K), U201.49 (PA13)
/02 MCU/SWO: D501.2 (K), D501.9 (K), U201.56 (PB3)
/02 MCU/USB_D+: R204.1, U201.46 (PA12), U501.6 (I/O1)
/02 MCU/USB_D-: R205.1, U201.45 (PA11), U501.4 (I/O2)
/02 MCU/USB_VBUS_SENSE: C501.1, R503.1, R504.2, U201.37 (PB15)
/03 Motor Control - Brake Chopper/BRAKE_GATE: Q301.4 (G), R306.1, R307.1, R308.2
/03 Motor Control - Brake Chopper/OUTH: R306.2, U301.2 (OUTH)
/03 Motor Control - Brake Chopper/OUTL: R307.2, U301.3 (OUTL)
/03 Motor Control - Gate Driver/03 Motor Control - Inverter/FET_GH_A: D803.2 (A), Q801.4 (G), R801.2
/03 Motor Control - Gate Driver/03 Motor Control - Inverter/FET_GH_B: D805.2 (A), Q803.4 (G), R815.2
/03 Motor Control - Gate Driver/03 Motor Control - Inverter/FET_GH_C: D808.2 (A), Q805.4 (G), R820.2
/03 Motor Control - Gate Driver/03 Motor Control - Inverter/FET_GL_A: D801.1 (K), D802.2 (A), Q802.4 (G), R802.2
/03 Motor Control - Gate Driver/03 Motor Control - Inverter/FET_GL_B: D804.1 (K), D806.2 (A), Q804.4 (G), R816.2
/03 Motor Control - Gate Driver/03 Motor Control - Inverter/FET_GL_C: D807.1 (K), D809.2 (A), Q806.4 (G), R821.2
/03 Motor Control - Gate Driver/03 Motor Control - Inverter/PHA: C801.2, C802.2, Q801.1 (S), Q801.2 (S), Q801.3 (S), Q802.5 (D), Q802.6 (D), Q802.7 (D), Q802.8 (D), R806.2
/03 Motor Control - Gate Driver/03 Motor Control - Inverter/PHB: C805.2, C806.2, Q803.1 (S), Q803.2 (S), Q803.3 (S), Q804.5 (D), Q804.6 (D), Q804.7 (D), Q804.8 (D), R809.2
/03 Motor Control - Gate Driver/03 Motor Control - Inverter/PHC: C809.2, C810.2, Q805.1 (S), Q805.2 (S), Q805.3 (S), Q806.5 (D), Q806.6 (D), Q806.7 (D), Q806.8 (D), R812.2
/03 Motor Control - Gate Driver/03 Motor Control - Inverter/SNUB_HA: C801.1, R803.1
/03 Motor Control - Gate Driver/03 Motor Control - Inverter/SNUB_HB: C805.1, R818.1
/03 Motor Control - Gate Driver/03 Motor Control - Inverter/SNUB_HC: C809.1, R823.1
/03 Motor Control - Gate Driver/03 Motor Control - Inverter/SNUB_LA: C802.1, R804.1
/03 Motor Control - Gate Driver/03 Motor Control - Inverter/SNUB_LB: C806.1, R819.1
/03 Motor Control - Gate Driver/03 Motor Control - Inverter/SNUB_LC: C810.1, R824.1
/03 Motor Control - Gate Driver/03 Motor Control - Inverter/SRC_LS_A: C804.2, Q802.1 (S), Q802.2 (S), Q802.3 (S), R804.2, R805.2
/03 Motor Control - Gate Driver/03 Motor Control - Inverter/SRC_LS_B: C807.2, Q804.1 (S), Q804.2 (S), Q804.3 (S), R817.2, R819.2
/03 Motor Control - Gate Driver/03 Motor Control - Inverter/SRC_LS_C: C811.2, Q806.1 (S), Q806.2 (S), Q806.3 (S), R822.2, R824.2
/03 Motor Control - Gate Driver/GHA: D803.1 (K), IC1.6 (GHA), R801.1
/03 Motor Control - Gate Driver/GHB: D805.1 (K), IC1.15 (GHB), R815.1
/03 Motor Control - Gate Driver/GHC: D808.1 (K), IC1.16 (GHC), R820.1
/03 Motor Control - Gate Driver/GLA: D802.1 (K), IC1.8 (GLA), R802.1
/03 Motor Control - Gate Driver/GLB: D806.1 (K), IC1.13 (GLB), R816.1
/03 Motor Control - Gate Driver/GLC: D809.1 (K), IC1.18 (GLC), R821.1
/03 Motor Control - Gate Driver/SENSE_UA: R807.1, R808.2
/03 Motor Control - Gate Driver/SENSE_UB: R810.1, R811.2
/03 Motor Control - Gate Driver/SENSE_UC: R813.1, R814.2
/05 Interface - Interconnects/D+: J503.A6 (DP1), J503.B6 (DP2), U501.1 (I/O1)
/05 Interface - Interconnects/D-: J503.A7 (DN1), J503.B7 (DN2), U501.3 (I/O2)
/05 Interface - Interconnects/USB_CC1: J503.A5 (CC1), R502.1
/05 Interface - Interconnects/USB_CC2: J503.B5 (CC2), R501.1
/BRAKE_SW: J501.N, Q301.5 (D), Q301.6 (D), Q301.7 (D), Q301.8 (D)
CHASSIS: C701.1, C702.1, C703.1, C704.1, D101.1, D102.1, H701.1 (1_1), H702.1 (1_1), H703.1 (1_1), H704.1 (1_1), J101.MP2, J102.MP2, J503.S1 (SHIELD), J503.S2 (SHIELD), J503.S3 (SHIELD), J503.S4 (SHIELD), R701.1, R702.1, R703.1, R704.1
GND: C102.2, C103.2, C104.2, C105.2, C106.2, C107.2, C108.2, C109.2, C110.2, C111.2, C112.2, C114.2, C115.2, C116.2, C117.2, C118.2, C119.2, C120.2, C121.2, C122.2, C123.2, C124.2, C125.2, C126.2, C127.2, C128.2, C129.2, C130.2, C131.2, C132.2, C133.2, C134.2, C135.2, C136.2, C137.2, C138.2, C139.2, C140.2, C141.2, C142.2, C143.2, C144.2, C145.2, C146.2, C147.2, C148.2, C149.2, C150.2, C151.2, C152.2, C153.2, C154.2, C155.2, C156.2, C157.2, C158.2, C159.2, C160.2, C161.2, C162.2, C163.2, C164.2, C165.2, C166.2, C167.2, C168.2, C169.2, C170.2, C171.2, C172.2, C173.2, C201.2, C202.2, C203.2, C204.2, C205.2, C206.2, C207.2, C208.2, C209.2, C210.2, C211.2, C212.2, C213.2, C214.2, C215.2, C216.2, C217.2, C302.2, C303.2, C308.2, C309.2, C401.2, C501.2, C503.2, C504.2, C701.2, C702.2, C703.2, C704.2, C803.2, C808.2, C812.2, D501.3 (A), D501.8 (A), D801.2 (A), D804.2 (A), D807.2 (A), IC1.32 (AGND), IC1.40 (PGND), IC1.41 (EP), J101.1, J102.1, J503.A1_B12 (GND), J503.B1_A12 (GND), Q301.1 (S), Q301.2 (S), Q301.3 (S), R102.2, R104.2, R305.1, R308.1, R402.2, R501.2, R502.2, R504.1, R701.2, R702.2, R703.2, R704.2, R805.1, R808.1, R811.1, R814.1, R817.1, R822.1, U101.1 (PGND), U101.4 (AGND), U101.5 (FB), U101.9 (PAD), U102.9 (GND), U103.2 (GND), U104.1 (PGND), U104.6 (AGND), U104.11 (PGND), U201.15 (VSS), U201.27 (VSSA), U201.31 (VSS), U201.47 (VSS), U201.63 (VSS), U301.4 (GND), U301.5 (IN-), U501.2 (GND)
unnamed: C301.2, IC1.3 (VCP)
unnamed: R806.1, R807.2
unnamed: R809.1, R810.2
unnamed: R812.1, R813.2
unnamed: C112.1, R102.1, U102.1 (MODE/SYNC)
unnamed: C125.1, U104.5 (VCC)
unnamed: R304.1, R305.2, U301.6 (IN+)
VBUS: C502.1, J503.A4_B9 (VBUS), J503.B4_A9 (VBUS), R503.2, U501.5 (VBUS)

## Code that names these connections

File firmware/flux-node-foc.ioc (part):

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Mcu.Name=STM32G474R(B-C-E)Tx
Mcu.Package=LQFP64
Mcu.UserName=STM32G474RETx
PA0.GPIOParameters=GPIO_Label
PA0.GPIO_Label=SENSE_U_C
PA0.Mode=IN1-Single-Ended
PA0.Signal=ADC2_IN1
PA1.GPIOParameters=GPIO_Label
PA1.GPIO_Label=SENSE_U_B
PA1.Mode=IN2-Single-Ended
PA1.Signal=ADC1_IN2
PA11.Mode=Device
PA11.Signal=USB_DM
PA12.Mode=Device
PA12.Signal=USB_DP
PA13.Mode=Trace_Asynchronous_SW
PA13.Signal=SYS_JTMS-SWDIO
PA14.Mode=Trace_Asynchronous_SW
PA14.Signal=SYS_JTCK-SWCLK
PA2.GPIOParameters=GPIO_Label
PA2.GPIO_Label=DRV_CAL
PA2.Signal=GPIO_Output
PA3.GPIOParameters=GPIO_Label
PA3.GPIO_Label=DRV_EN
PA3.Signal=GPIO_Output
PA4.GPIOParameters=GPIO_Speed,GPIO_Label
PA4.GPIO_Label=SPI1_DRV_CS
PA4.GPIO_Speed=GPIO_SPEED_FREQ_MEDIUM
PA4.Signal=GPIO_Output
PA5.Mode=Full_Duplex_Master
PA5.Signal=SPI1_SCK
PA6.Mode=Full_Duplex_Master
PA6.Signal=SPI1_MISO
PA7.Mode=Full_Duplex_Master
PA7.Signal=SPI1_MOSI
PA8.GPIOParameters=GPIO_Label
PA8.GPIO_Label=SENSE_TEMP_FET
PA8.Mode=IN1-Single-Ended
PA8.Signal=ADC5_IN1
PA9.GPIOParameters=GPIO_Label
PA9.GPIO_Label=SENSE_TEMP_MOT
PA9.Mode=IN2-Single-Ended
PA9.Signal=ADC5_IN2
PB0.GPIOParameters=GPIO_Label
PB0.GPIO_Label=DRV_SOA
PB0.Mode=IN12-Single-Ended
PB0.Signal=ADC3_IN12
PB1.GPIOParameters=GPIO_Label
PB1.GPIO_Label=DRV_SOB
PB1.Mode=IN12-Single-Ended
PB1.Signal=ADC1_IN12
PB11.GPIOParameters=GPIO_Label
PB11.GPIO_Label=EXT_FAN
PB11.Signal=S_TIM2_CH4
PB12.GPIOParameters=GPIO_Label
PB12.GPIO_Label=SENSE_TEMP_BRAKE
PB12.Mode=IN3-Single-Ended
PB12.Signal=ADC4_IN3
PB13.GPIOParameters=GPIO_Label
PB13.GPIO_Label=SENSE_VBAT
PB13.Mode=IN5-Single-Ended
PB13.Signal=ADC3_IN5
PB14.GPIOParameters=GPIO_Label
PB14.GPIO_Label=DRV_PWM_LB
PB14.Mode=PWM Generation2 CH2 CH2N
PB14.Signal=TIM1_CH2N
PB15.GPIOParameters=GPIO_Label
PB15.GPIO_Label=SENSE_USB_VBUS
PB15.Mode=IN5-Single-Ended
PB15.Signal=ADC4_IN5
PB2.GPIOParameters=GPIO_Label
PB2.GPIO_Label=DRV_SOC
PB2.Mode=IN12-Single-Ended
PB2.Signal=ADC2_IN12
PB3.Mode=Trace_Asynchronous_SW
PB3.Signal=SYS_JTDO-SWO
PB4.GPIOParameters=GPIO_Label
PB4.GPIO_Label=LED_PWR
PB4.Signal=GPIO_Output
PB5.Mode=FDCAN_Activate
PB5.Signal=FDCAN2_RX
PB6.Mode=FDCAN_Activate
PB6.Signal=FDCAN2_TX
PB7.Mode=I2C
PB7.Signal=I2C1_SDA
PB8-BOOT0.Mode=I2C
PB8-BOOT0.Signal=I2C1_SCL
PB9.GPIOParameters=GPIO_Label,GPIO_FM9
PB9.GPIO_FM9=__NULL
PB9.GPIO_Label=DRV_PWM_LA
PB9.Mode=PWM Generation3 CH3 CH3N
PB9.Signal=TIM1_CH3N
PC0.GPIOParameters=GPIO_Label
PC0.GPIO_Label=DRV_PWM_HC
PC0.Signal=S_TIM1_CH1
PC1.GPIOParameters=GPIO_Label
PC1.GPIO_Label=DRV_PWM_HB
PC1.Signal=S_TIM1_CH2
PC10.Mode=Full_Duplex_Master
PC10.Signal=SPI3_SCK
PC11.Mode=Full_Duplex_Master
PC11.Signal=SPI3_MISO
PC12.Mode=Full_Duplex_Master
PC12.Signal=SPI3_MOSI
PC13.GPIOParameters=GPIO_Label
PC13.GPIO_Label=DRV_PWM_LC
PC13.Mode=PWM Generation1 CH1 CH1N
PC13.Signal=TIM1_CH1N
PC14-OSC32_IN.GPIOParameters=GPIO_Label
PC14-OSC32_IN.GPIO_Label=SPI1_AUX1_CS
PC14-OSC32_IN.Signal=GPIO_Output
PC2.GPIOParameters=GPIO_Label
PC2.GPIO_Label=PWM_DRV_HA
PC2.Signal=S_TIM1_CH3
PC3.GPIOParameters=GPIO_Label
PC3.GPIO_Label=SENSE_U_A
PC3.Mode=IN9-Single-Ended
PC3.Signal=ADC2_IN9
PC4.GPIOParameters=GPIO_Label
PC4.GPIO_Label=DRV_nFAULT
PC4.Signal=GPXTI4
PC5.GPIOParameters=GPIO_Speed,GPIO_Label
PC5.GPIO_Label=SPI1_MAG_CS
PC5.GPIO_Speed=GPIO_SPEED_FREQ_MEDIUM
PC5.Signal=GPIO_Output
PC9.GPIOParameters=GPIO_Label
PC9.GPIO_Label=BRAKE_PWM
PC9.Signal=S_TIM3_CH4
PD2.GPIOParameters=GPIO_Label
PD2.GPIO_Label=LED_DBG
PD2.Signal=GPIO_Output
PF0-OSC_IN.Mode=HSE-External-Oscillator
PF0-OSC_IN.Signal=RCC_OSC_IN
PF1-OSC_OUT.Mode=HSE-External-Oscillator
PF1-OSC_OUT.Signal=RCC_OSC_OUT
RCC.HSE_VALUE=8000000
RCC.SYSCLKFreq_VALUE=170000000
RCC.SYSCLKSource=RCC_SYSCLKSOURCE_PLLCLK
board=custom

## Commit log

2026-06-07 Moved PCB files into a seperate folder
2026-06-07 Added a README file with the current design goals
2026-06-07 Setup scematic hirarchy and different sheets
2026-06-08 Added a firmware directory with the STM32 pinout config file
2026-06-08 Setup project structure with organised sub-sheets
2026-06-08 Added custom project symbol library
2026-06-08 Added custom project footprint library
2026-06-11 Set up gate driver circuitry according to the datasheet
2026-06-11 Added two XT-60 power connectors for daisy chaining multiple nodes together
2026-06-11 Power conditioning and generation of +3V3, +A3V3, +5V and +12V from VBat
2026-06-11 Planned MCU pinout and wired it to the gate driver
2026-06-11 Updated project footprint and symbol library
2026-06-12 Added all missing pins and functionality to the MCU pinout
2026-06-14 Added new symbols and related footprints
2026-06-14 Switched some sense pins for better ADC separation and utilisation
2026-06-14 Ported CubeMX pinout to KiCad; Setup all the main busses to communicate with peripherals
2026-06-14 Added a sheet for the brake chopper circuitry
2026-06-14 Added four mounting holes connected to chassis with decoupling to gnd and one single connection from chassis to gnd
2026-06-14 Added USB and SWD ports with necessary circuitry and ESD protection
2026-06-14 Created blockout and connections of all the major parts
2026-06-14 Updated project structure
2026-06-14 Implemented brake chopper control with low side mosfet
2026-06-14 Added VBAT sensing via a voltage divider to stay within the MCU 3V3 limit
2026-06-14 Added the XT-30 (2-2) connector for an external brake power resistor and a thermistor
2026-06-14 Added fiducials for the top and bottom PCB side
2026-06-15 Created a sheet template
2026-06-16 Updated pin configuration slightly and setup timers and adcs correctly
2026-06-16 Extended symbol and footrpint library
2026-06-16 Unified all different LCSC part numbers of the same exact components to just one variant
2026-06-16 Unified naming sceme and made the minimum hole size 0.3mm accoriding to JLCPCB capabilities
2026-06-16 Updated silkscreen designators to a uniform stroke width of 0.15 mm and size of 0.8 by 0.8 mm
2026-06-16 Utilized new connector footprint
2026-06-16 Some minor changes to the annotations
2026-06-16 Moved readme to the project root
2026-06-16 Added CERN Open Hardware Licence Version 2
2026-06-16 Add .gitignore file to exclude build artifacts and local metadata
2026-06-16 Dumped ChatGPT memories into a structured README file
2026-06-16 New docs/ structure
2026-06-16 First basic documentation
2026-06-16 Reorganised pdb folder structure to acomodate seperate sheets folder and an erxternal lib folder
2026-06-16 Initial C firmware template by CubeMX

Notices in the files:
README.md:
28. License:
A license has not yet been finalized.
Before publishing the repository, choose separate or compatible licenses for:
- Hardware design files
- Firmware
- Documentation
Common choices include CERN-OHL for hardware and MIT, BSD, GPL, or Apache-2.0 for firmware. The final choice should reflect whether commercial reuse and closed-source derivatives are intended to be allowed.
